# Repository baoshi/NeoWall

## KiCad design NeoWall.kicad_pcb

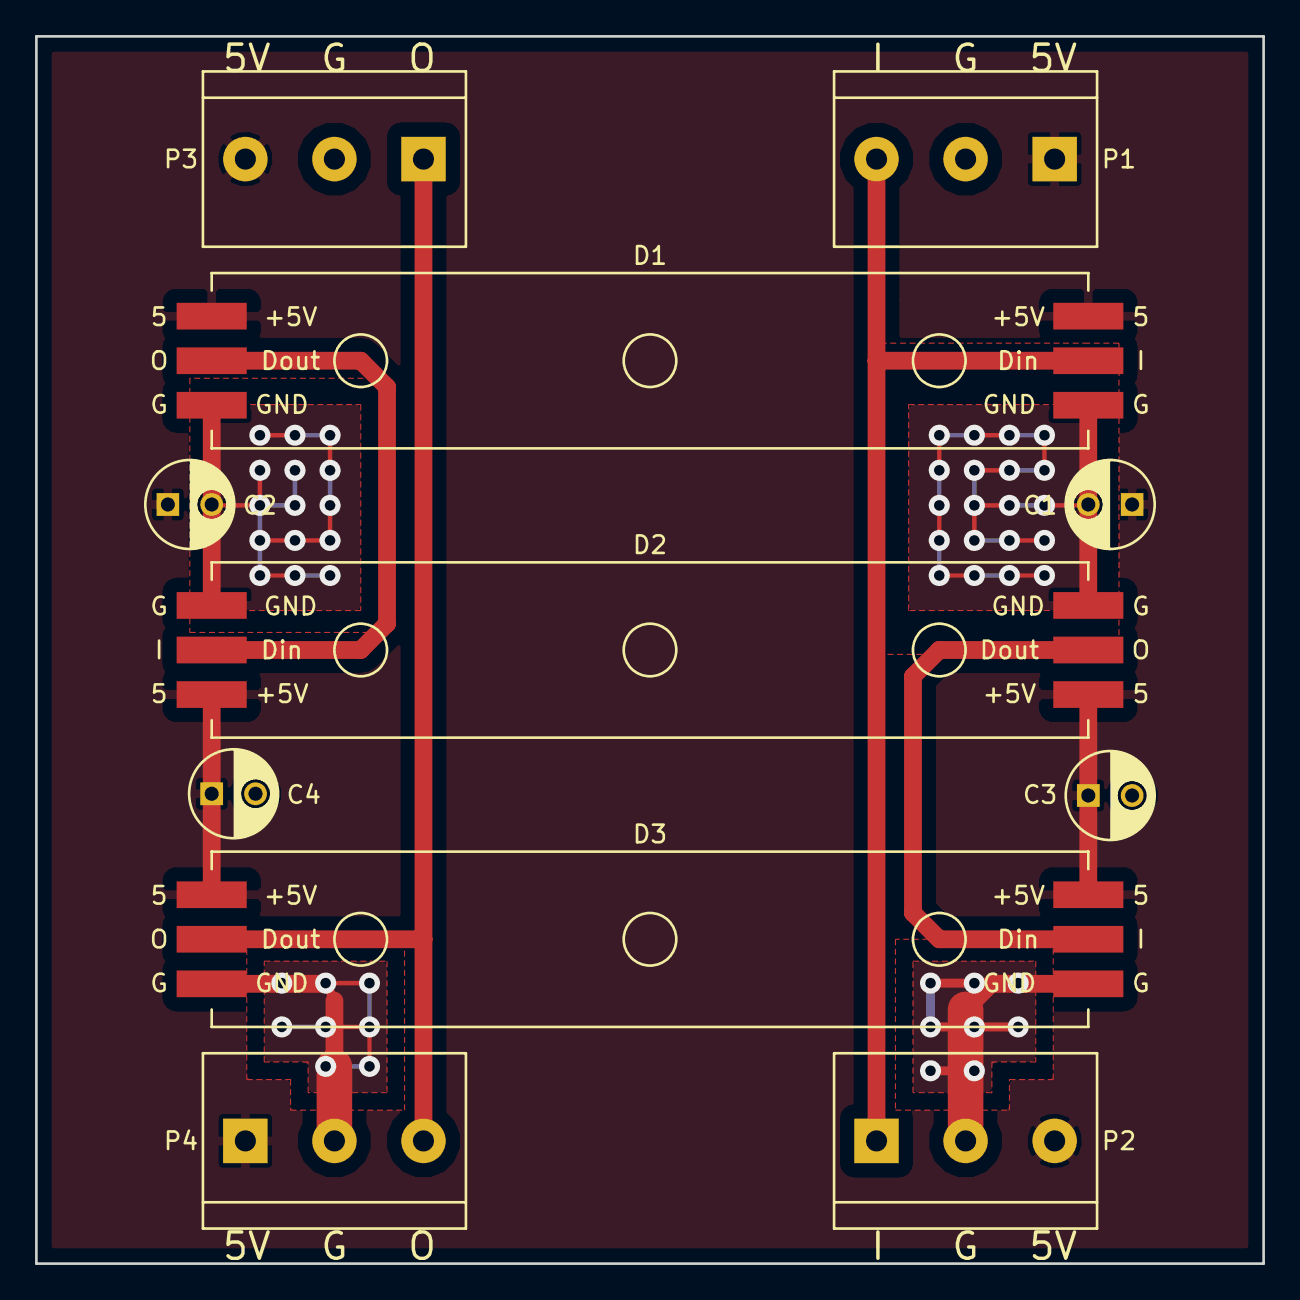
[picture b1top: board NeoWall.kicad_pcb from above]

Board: 2 copper layers, 70.0 x 70.0 mm, 15 parts (0 on the bottom side), 6 nets.

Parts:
C1, C2, C3, C4: 10u; C_Radial_D5_L6_P2.5
D1, D2, D3: Neopixelx3
MK1, MK2, MK3, MK4: Mounting_Hole; MountingHole_3.2mm_M3
P1, P2, P3, P4: CONN_01X03; bornier3

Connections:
+5V: C1.1, C2.1, C3.1, C4.1, D1.3, D1.4, D2.3, D2.4, D3.3, D3.4, P1.1, P2.3, P3.3, P4.1
GND: C1.2, C2.2, C3.2, C4.2, D1.1, D1.6, D2.1, D2.6, D3.1, D3.6, P1.2, P2.2, P3.2, P4.2
unnamed: D1.2, P1.3, P2.1
unnamed: D1.5, D2.2
unnamed: D2.5, D3.2
unnamed: D3.5, P3.1, P4.3

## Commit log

2017-05-10 Optimize cap positions
